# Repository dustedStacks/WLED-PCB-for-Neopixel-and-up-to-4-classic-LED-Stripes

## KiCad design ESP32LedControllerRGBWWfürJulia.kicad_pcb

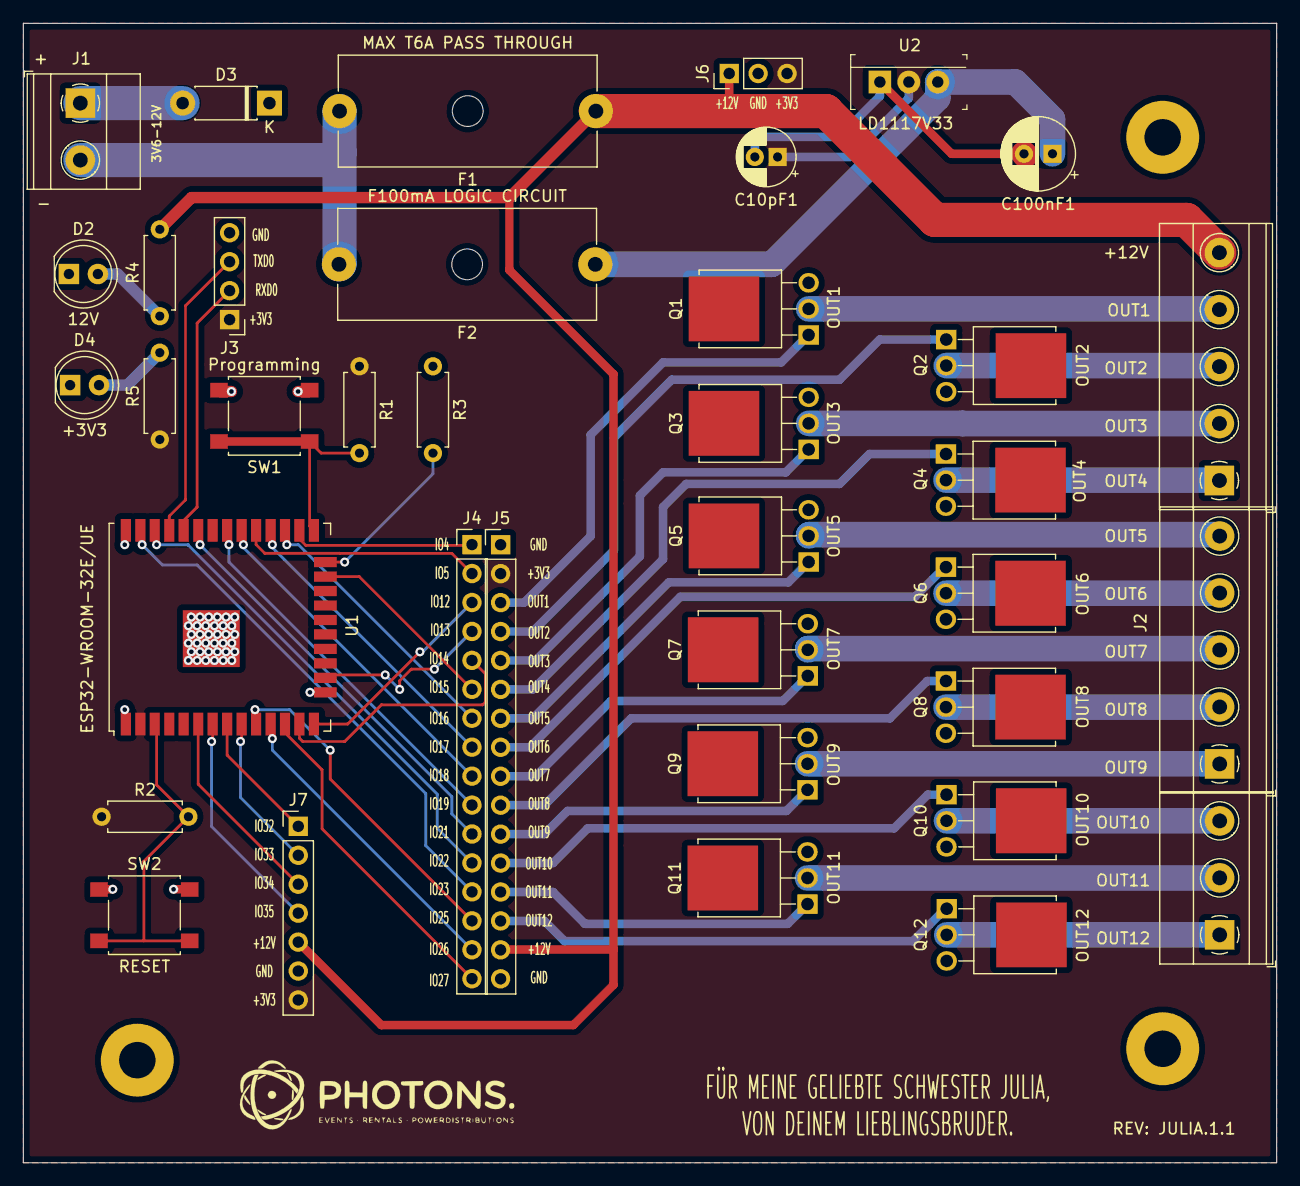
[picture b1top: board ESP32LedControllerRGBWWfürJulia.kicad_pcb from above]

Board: 2 copper layers, 110.0 x 100.0 mm, 37 parts (0 on the bottom side), 57 nets.

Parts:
C10pF1: CP; CP_Radial_D5.0mm_P2.00mm
C100nF1: CP; CP_Radial_D6.3mm_P2.50mm
D2: 12V; LED_D5.0mm
D3: DIODE; D_DO-41_SOD81_P7.62mm_Horizontal
D4: +3V3; LED_D5.0mm
F1: MAX T6A PASS THROUGH; Fuseholder_Cylinder-5x20mm_Schurter_0031_8201_Horizontal_Op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
F2: F100mA LOGIC CIRCUIT; Fuseholder_Cylinder-5x20mm_Schurter_0031_8201_Horizontal_Op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
J1: Screw_Terminal_01x02; TerminalBlock_Phoenix_MKDS-1,5-2_1x02_P5.00mm_Horizontal
J2, J2#3: Screw_Terminal_01x05; TerminalBlock_Phoenix_MKDS-1,5-5_1x05_P5.00mm_Horizontal
J2#2: Screw_Terminal_01x03; TerminalBlock_Phoenix_MKDS-1,5-3_1x03_P5.00mm_Horizontal
J3: Conn_01x04_Male; PinHeader_1x04_P2.54mm_Vertical
J4, J5: Conn_01x16_Male; PinHeader_1x16_P2.54mm_Vertical
J6: Conn_01x03_Male; PinHeader_1x03_P2.54mm_Vertical
J7: Conn_01x07_Male; PinHeader_1x07_P2.54mm_Vertical
Q1, Q2, Q3, Q4, Q5, Q6, Q7, Q8, Q9, Q10, Q11, Q12: IRLU024NPBF; TO-251-3-1EP_Horizontal_TabDown
R1, R2, R3: 10K; R_Axial_DIN0207_L6.3mm_D2.5mm_P7.62mm_Horizontal
R4: 470Ohm; R_Axial_DIN0207_L6.3mm_D2.5mm_P7.62mm_Horizontal
R5: 4,7Ohm; R_Axial_DIN0207_L6.3mm_D2.5mm_P7.62mm_Horizontal
SW1: Programming; SW_SPST_B3S-1000
SW2: RESET; SW_SPST_B3S-1000
U1: ESP32-WROOM-32E/UE; ESP32-WROOM-32U
U2: LD1117V33; TO-220-3

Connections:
+3V3: C10pF1.1, J3.1, J5.2, J6.3, J7.7, R1.1, R2.1, R5.1, U1.2, U2.2
+12V: F1.1, J2#3.1, J5.15, J6.1, J7.5, R4.2
/IO4: J4.1, U1.26
/IO5: J4.2, U1.29
/IO12: J4.3, U1.14
/IO13: J4.4, U1.16
/IO14: J4.5, U1.13
/IO15: J4.6, U1.23
/IO16: J4.7, U1.27
/IO17: J4.8, U1.28
/IO18: J4.9, U1.30
/IO19: J4.10, U1.31
/IO21: J4.11, U1.33
/IO22: J4.12, U1.36
/IO23: J4.13, U1.37
/IO25: J4.14, U1.10
/IO26: J4.15, U1.11
/IO27: J4.16, U1.12
/OUT1: J5.3, Q1.1
/OUT2: J5.4, Q2.1
/OUT3: J5.5, Q3.1
/OUT4: J5.6, Q4.1
/OUT5: J5.7, Q5.1
/OUT6: J5.8, Q6.1
/OUT7: J5.9, Q7.1
/OUT8: J5.10, Q8.1
/OUT9: J5.11, Q9.1
/OUT10: J5.12, Q10.1
/OUT11: J5.13, Q11.1
/OUT12: J5.14, Q12.1
GND: C10pF1.2, C100nF1.2, D2.1, D3.1, D4.1, J3.4, J5.1, J5.16, J6.2, J7.6, Q1.3, Q2.3, Q3.3, Q4.3, Q5.3, Q6.3, Q7.3, Q8.3, Q9.3, Q10.3, Q11.3, Q12.3, R3.1, SW1.2, SW2.1, U1.1, U1.15, U1.38, U1.39, U2.1
unnamed: C100nF1.1, F2.1, U2.3
unnamed: F1.2, F2.2, J1.2
unnamed: D2.2, R4.1
unnamed: D3.2, J1.1
unnamed: D4.2, R5.2
unnamed: J2#3.2, Q1.2
unnamed: J2#3.3, Q2.2
unnamed: J2#3.4, Q3.2
unnamed: J2#3.5, Q4.2
unnamed: J2.6, Q5.2
unnamed: J2.7, Q6.2
unnamed: J2.8, Q7.2
unnamed: J2.9, Q8.2
unnamed: J2.10, Q9.2
unnamed: J2#2.11, Q10.2
unnamed: J2#2.12, Q11.2
unnamed: J2#2.13, Q12.2
unnamed: J3.2, U1.34
unnamed: J3.3, U1.35
unnamed: J7.1, U1.8
unnamed: J7.2, U1.9
unnamed: J7.3, U1.6
unnamed: J7.4, U1.7
unnamed: R1.2, SW1.1, U1.25
unnamed: R2.2, SW2.2, U1.3
unnamed: R3.2, U1.24

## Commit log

2022-02-25 First Issue (V:Julia1.1)
    Erster Release der Arbeitsdaten

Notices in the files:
ESP32LedControllerRGBWWfürJulia.kicad_pcb:
COPYRIGHT BY DUSTIN SCHINDLER
